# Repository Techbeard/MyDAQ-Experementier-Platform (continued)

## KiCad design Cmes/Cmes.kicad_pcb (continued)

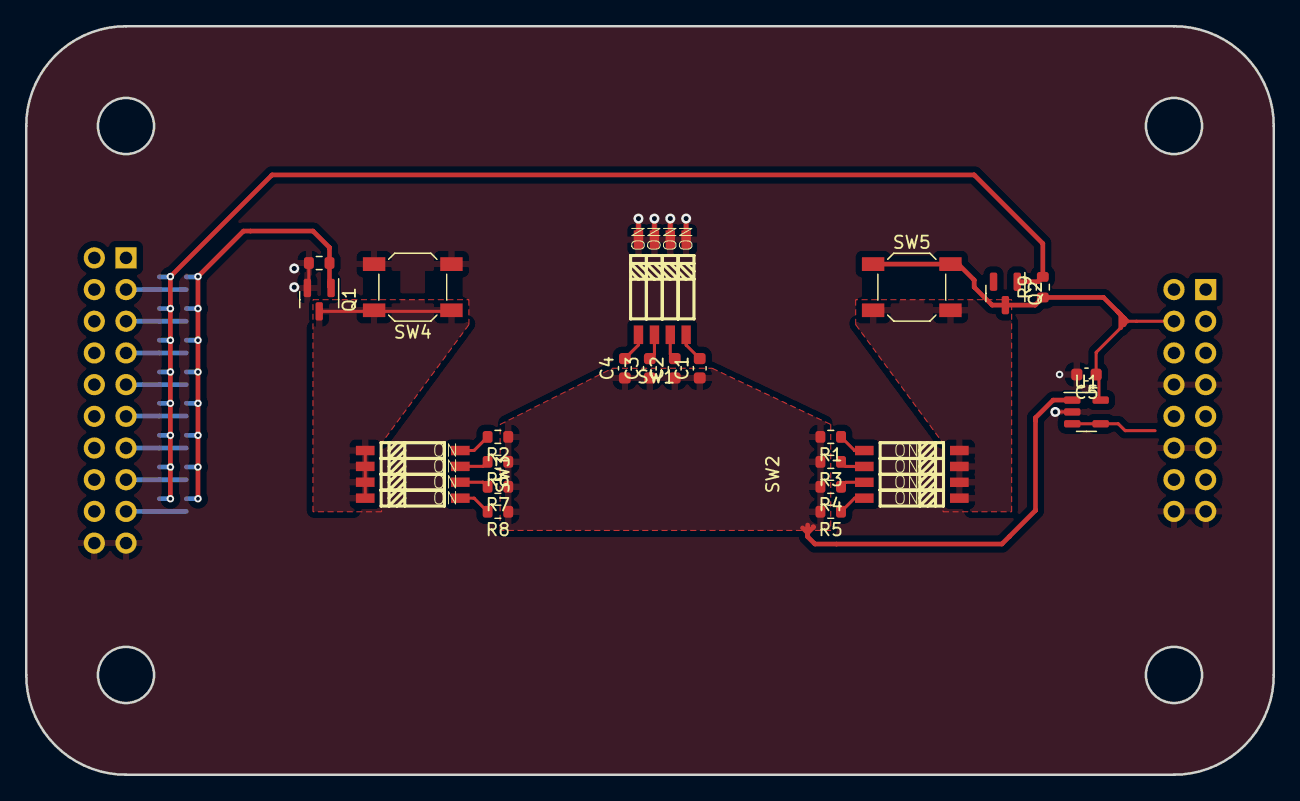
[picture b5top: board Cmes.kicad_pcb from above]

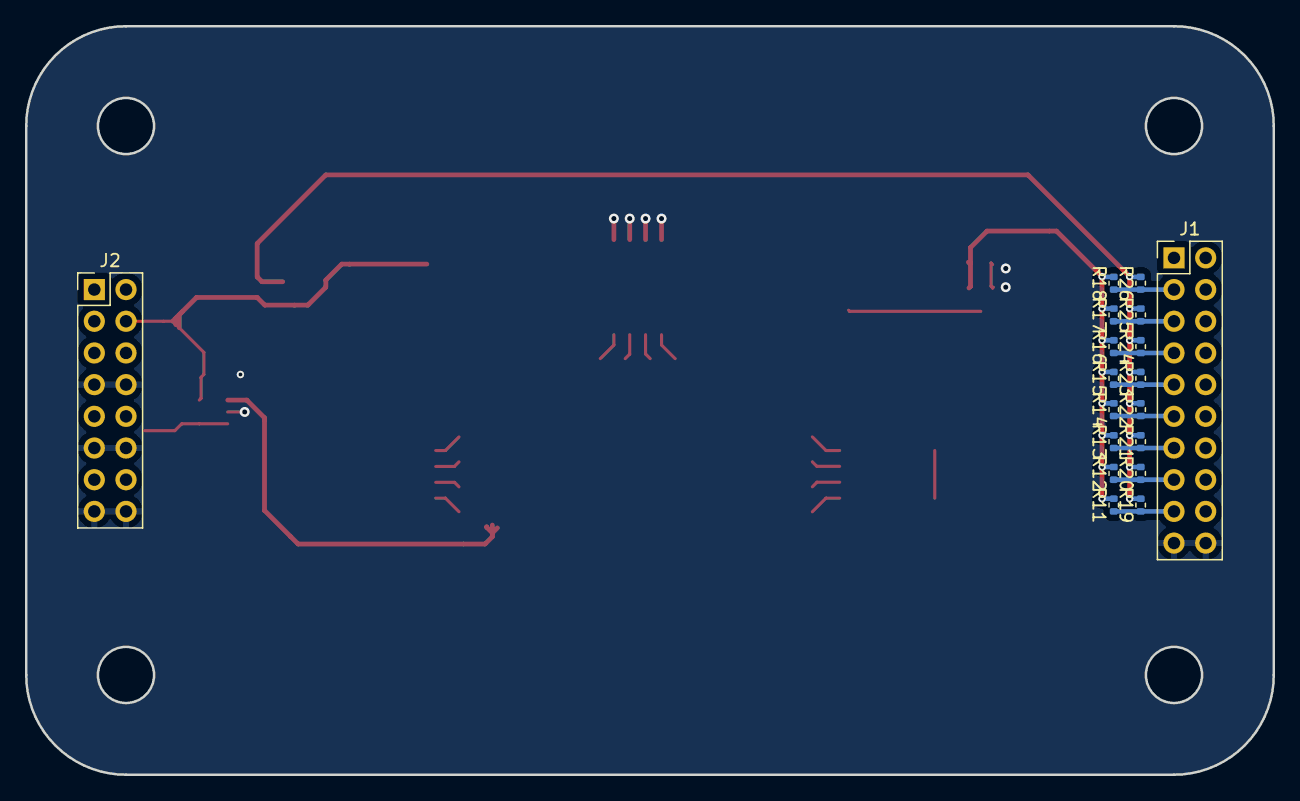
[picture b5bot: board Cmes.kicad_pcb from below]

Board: 2 copper layers, 100.0 x 60.0 mm, 41 parts (18 on the bottom side), 28 nets.

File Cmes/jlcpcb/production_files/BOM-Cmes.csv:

Comment,Designator,Footprint,LCSC
SW_Push,SW4,SW_SPST_SKQG_WithStem,
10k,R3,R_0603_1608Metric,
10k,R4,R_0603_1608Metric,
LM321,U1,SOT-23-5,
C,C4,C_0603_1608Metric,
10k,R7,R_0603_1608Metric,
C,C3,C_0603_1608Metric,
SW_DIP_x04,SW3,SW-SMD_8P-L6.7-W5.4-P1.27-LS8.5,
100n,C5,C_0603_1608Metric,
10k,R9,R_0603_1608Metric,
C,C1,C_0603_1608Metric,
10k,R10,R_0603_1608Metric,
10k,R2,R_0603_1608Metric,
10k,R5,R_0603_1608Metric,
SW_DIP_x04,SW1,SW-SMD_8P-L6.7-W5.4-P1.27-LS8.5,
10k,R1,R_0603_1608Metric,
SW_DIP_x04,SW2,SW-SMD_8P-L6.7-W5.4-P1.27-LS8.5,
SW_Push,SW5,SW_SPST_SKQG_WithStem,
AO3401A,Q2,SOT-23,
10k,R8,R_0603_1608Metric,
AO3400A,Q1,SOT-23,
10k,R6,R_0603_1608Metric,
C,C2,C_0603_1608Metric,
0,R20,R_0402_1005Metric,
0,R23,R_0402_1005Metric,
0,R24,R_0402_1005Metric,
0,R14,R_0402_1005Metric,
0,R26,R_0402_1005Metric,
0,R17,R_0402_1005Metric,
Conn_02x10_Odd_Even,J1,PinHeader_2x10_P2.54mm_Vertical,
0,R18,R_0402_1005Metric,
0,R15,R_0402_1005Metric,
0,R12,R_0402_1005Metric,
0,R16,R_0402_1005Metric,
0,R13,R_0402_1005Metric,
0,R25,R_0402_1005Metric,
0,R22,R_0402_1005Metric,
0,R11,R_0402_1005Metric,
Conn_02x08_Odd_Even,J2,PinHeader_2x08_P2.54mm_Vertical,
0,R19,R_0402_1005Metric,
0,R21,R_0402_1005Metric,

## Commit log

2025-11-19 add Files
